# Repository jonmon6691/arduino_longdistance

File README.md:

# arduino_LongDistance
An improvement to [arduino_RustysCalling](https://github.com/jonmon6691/arduino_rustyscalling/) that increases range, responsiveness, battery life, reduces complexity, and even folds your laundry!

## Todo
* Clean up phone wiring, can I get a new handset??
* Add wiring for dial
* Power button
  * Toggle button with LED
  * LED can be powered directly with 3.3V output, brightness is good at 2k series R, current is only .5ma

## Remote
This module is simply a button and a LoRa transmitter.

While the button is pressed, the remote transmitts packets as fast as it can. Otherwise it's idle, not sending anything.

Note: To maximize the packet rate (and therefore increase the responsiveness), the modems use the `.setModemConfig(RH_RF95::Bw500Cr45Sf128)` setting to optimize speed at the cost of distance. In practice this results in a packet every 8ms. The range appears to be more than sufficient, even when the rx is closed inside the phone.

### Feather Option
https://www.adafruit.com/product/3178

Battery life for a SAMD Radiofruit with a 350mAh little lipo pack is about 1 week. Would be nice if this was replaceable...
<br />
__Note:__ that's with 1mA while asleep (not using RFM sleep), 120mA while transmitting

### BSN3 Option
https://github.com/EasySensors/ButtonSizeNode3

Programs just like an Arduino Pro Mini, directly with an FTDI cable. Using sleep state for the Mega and for radio its down to 4 microamps. The two CR2032's (255mAh @ 6.5V) should last 7 years!!! I need to double check my ammeter tbh

## Phone
The LoRa receiver also orchestrates the phones other functions

### Ringer
Every time the phone receives a LoRa packet, it will run the ringer for the next 20 milliseconds. Since the packets come every 8ms, this means the ringer will stay on without interruption while the remote button held down, and will ring for about 20ms after its released. Which isn't noticeable.

To turn on the ringer, the microcontroller drives the gate of an N-channel FET with a 3.3k pulldown resistor. That FET provides a path to ground for a ringer module which converts the DC of a 9V battery into 70V 20Hz AC to power the ringer directly.

* Experiments on making the ringer louder
  * 2x A23 in parallel,(172mA) Not significantly louder, but less voltage drop during ringing (4v drop vs 2v drop) and will probably last a lot longer
  * 12v wall wart, (210mA) not significantly louder, no voltage drop at all while ringing.
  * 1x 9V, (160mA) not significantly quieter, but could in theory last a lot longer, like 20x
  * 2x A23 in series (24v) doesn't work, but thankfully, doesn't break the ringer either
  * 2x 9V in series (18.5v) doesn't work, but thankfully, doesn't break the ringer either
  * __Conclusion__: Using single 9V battery for convinience and longevity
* Power consumption
  * ESP + Lora listening = 81mA! 68mA of that is from the ESP by itself. Surely there's a way to lower this, maybe Wifi or BT is on??
  * Audio FX board: 29mA idle

### Playing audio
When the handset is lifted off the cradle, the phone will play a random audio file through the speaker.

The audio is generated by an Adafruit SFX board which is controlled using UART from the LoRa receiver module.

When the handset is placed back on the cradle, the audio will stop.

When the dial is turned and the handset is off the cradle, the current audio will be interrupted and the phone will play a giggling noise. When it's released, it will start a new audio.

The ground of the audio board is driven with another FET like the ringer module so that the power consumption can be cut by the main controller.

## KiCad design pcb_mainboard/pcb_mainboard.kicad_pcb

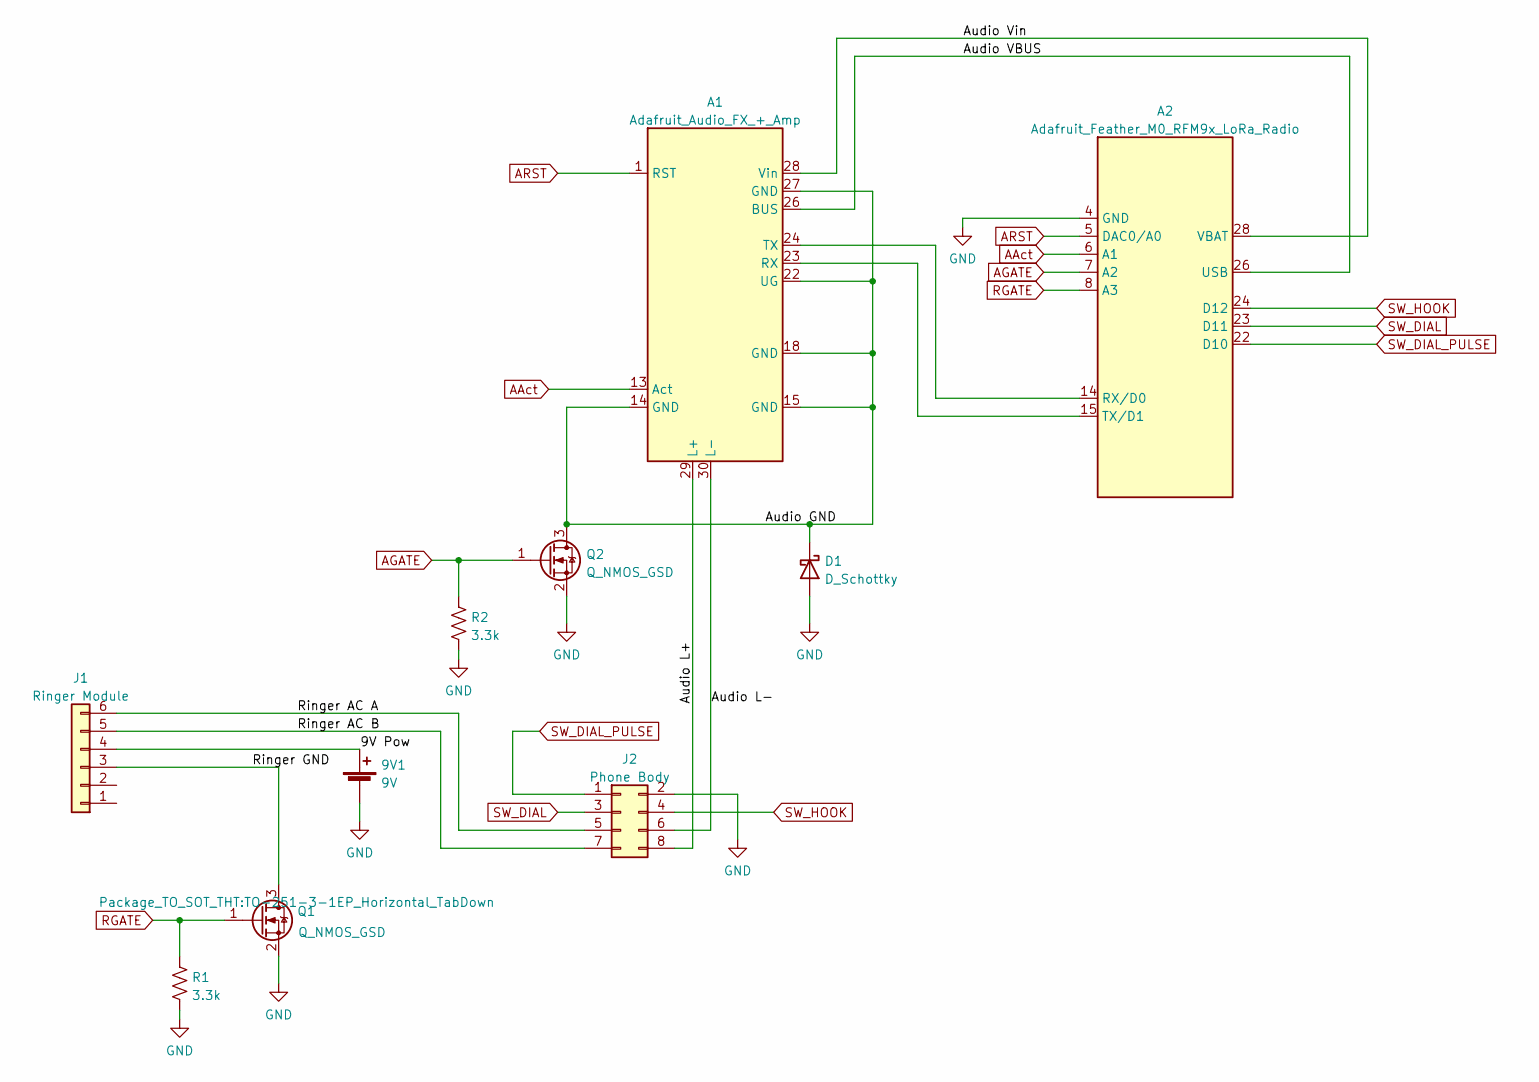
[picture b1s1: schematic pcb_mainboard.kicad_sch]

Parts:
9V1: 9V; PinHeader_1x02_P2.54mm_Vertical
A1: Adafruit_Audio_FX_+_Amp; Adafruit Audio FX + Amp
A2: Adafruit_Feather_M0_RFM9x_LoRa_Radio; Adafruit_Feather_M0_RFM
D1: D_Schottky; D_DO-41_SOD81_P7.62mm_Horizontal
J1: Ringer Module; PinHeader_1x06_P2.54mm_Vertical
J2: Phone Body; PinSocket_2x04_P2.54mm_Vertical
Q1, Q2: Q_NMOS_GSD; TO-251-3-1EP_Horizontal_TabDown
R1, R2: 3.3k; R_Axial_DIN0204_L3.6mm_D1.6mm_P5.08mm_Horizontal

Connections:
/9V Pow: 9V1.1 (+), J1.4
/Audio GND: A1.14 (GND), A1.15 (GND), A1.18 (GND), A1.22 (UG), A1.27 (GND), D1.1 (K), Q2.3 (D)
/Audio L+: A1.29 (L+), J2.8
/Audio L-: A1.30 (L-), J2.6
/Audio VBUS: A1.26 (BUS), A2.26 (USB)
/Audio Vin: A1.28 (Vin), A2.28 (VBAT)
/Ringer AC A: J1.6, J2.5
/Ringer AC B: J1.5, J2.7
/Ringer GND: J1.3, Q1.3 (D)
AAct: A1.13 (Act), A2.6 (A1)
AGATE: A2.7 (A2), Q2.1 (G), R2.1
ARST: A1.1 (RST), A2.5 (DAC0/A0)
GND: 9V1.2 (-), A2.4 (GND), D1.2 (A), J2.2, Q1.2 (S), Q2.2 (S), R1.2, R2.2
unnamed: A1.23 (RX), A2.15 (TX/D1)
unnamed: A1.24 (TX), A2.14 (RX/D0)
RGATE: A2.8 (A3), Q1.1 (G), R1.1
SW_DIAL: A2.23 (D11), J2.3
SW_DIAL_PULSE: A2.22 (D10), J2.1
SW_HOOK: A2.24 (D12), J2.4

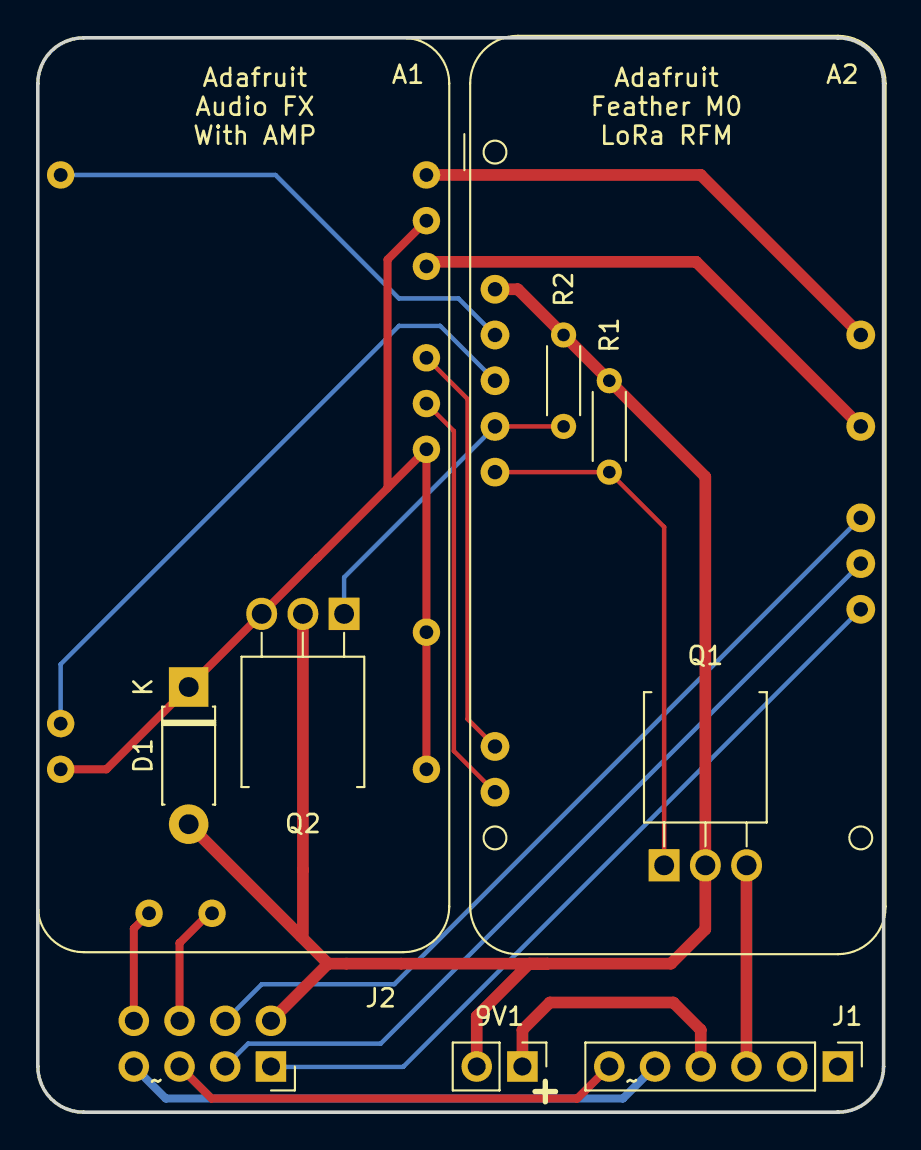
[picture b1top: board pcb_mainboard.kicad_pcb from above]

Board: 2 copper layers, 47.0 x 59.7 mm, 10 parts (0 on the bottom side), 19 nets.

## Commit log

2024-07-19 Initial commit!
2024-07-19 Add todo list
2024-07-20 R and D
2024-07-24 fix capitalization
2024-07-27 Fix import low power lab was the wrong choice.
2024-08-04 PCB v1
2024-08-04 News
2024-08-05 Got BSN3 working
2024-08-18 sound board state machine
2024-08-18 news flash bucko
2024-08-18 V1 board as sent to oshpark
